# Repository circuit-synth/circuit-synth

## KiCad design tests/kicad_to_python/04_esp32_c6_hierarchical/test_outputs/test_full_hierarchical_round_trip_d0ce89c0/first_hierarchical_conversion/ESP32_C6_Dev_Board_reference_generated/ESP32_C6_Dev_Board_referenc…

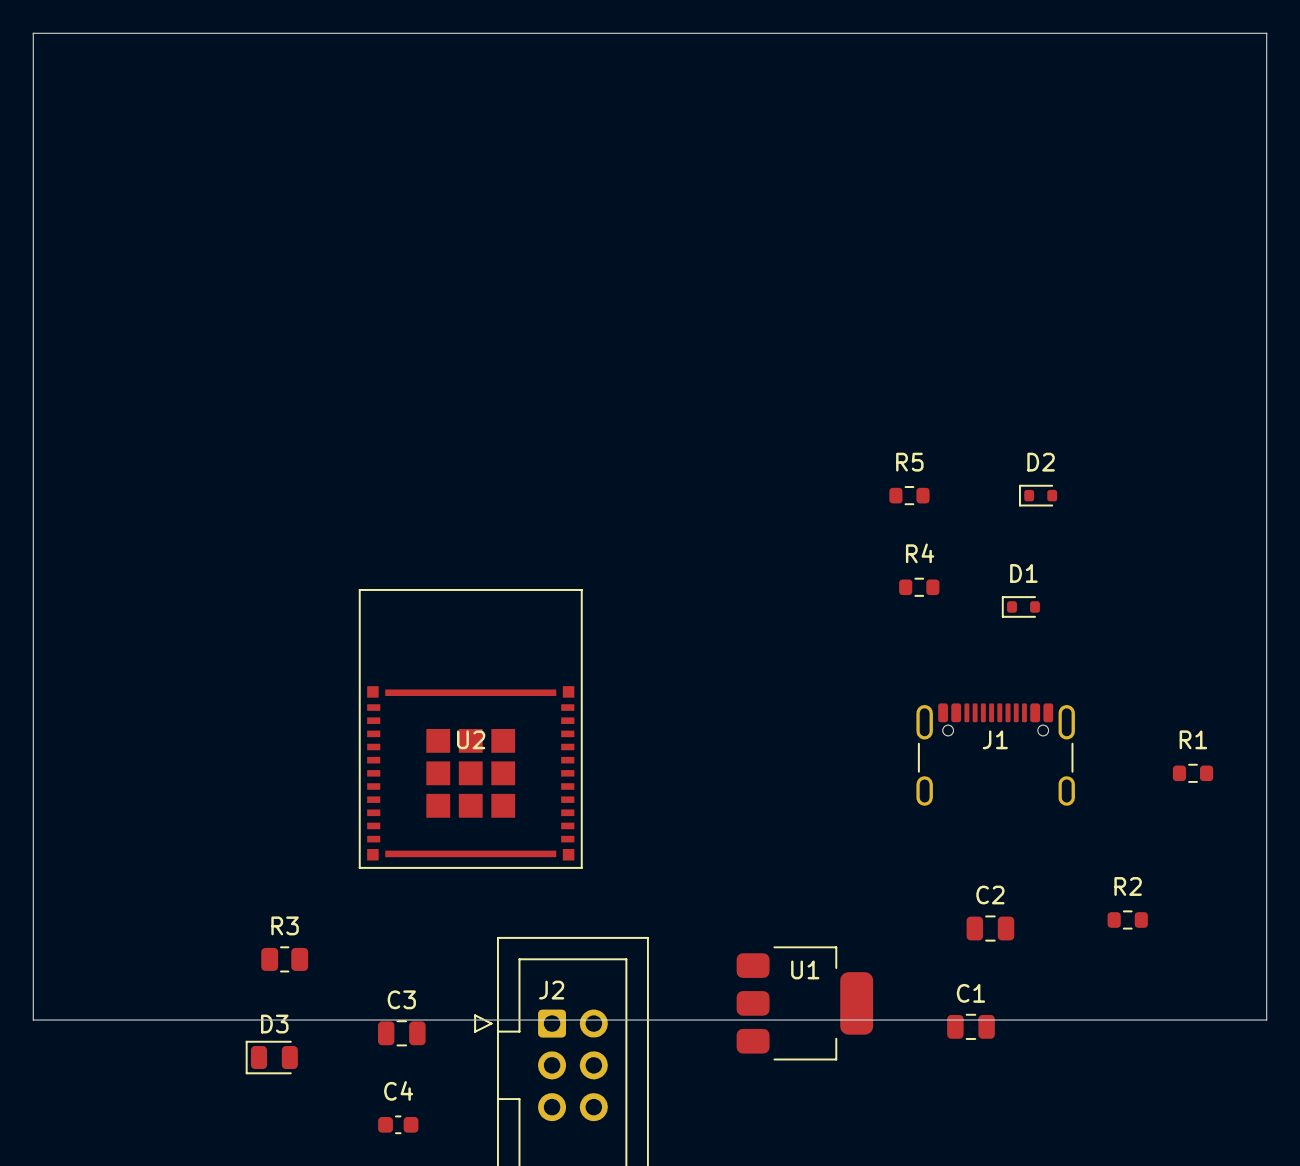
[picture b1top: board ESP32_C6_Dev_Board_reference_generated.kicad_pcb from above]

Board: 2 copper layers, 75.0 x 60.0 mm, 16 parts (0 on the bottom side), 15 nets, no tracks yet.

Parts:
C1, C2: 10uF; C_0805_2012Metric
C3: 22uF; C_0805_2012Metric
C4: 100nF; C_0603_1608Metric
D1, D2: D_SOD-523
D3: LED_0805_2012Metric
J1: USB_C_Receptacle_GCT_USB4105-xx-A_16P_TopMnt_Horizontal
J2: IDC-Header_2x03_P2.54mm_Vertical
R1, R2: 5.1k; R_0603_1608Metric
R3: 330; R_0805_2012Metric
R4, R5: 22; R_0603_1608Metric
U1: SOT-223-3_TabPin2
U2: ESP32-C6-MINI-1

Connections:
DEBUG_EN: J2.1, U2.8
DEBUG_IO0: J2.6, U2.12
DEBUG_RX: J2.5, U2.30
DEBUG_TX: J2.3, U2.31
ESP32_C6_MCU/N$3: D3.2, R3.2
GND: C1.2, C2.2, C3.2, C4.2, D1.2, D2.2, D3.1, J1.A1, J1.A12, J1.B1, J1.B12, J1.S1, J2.4, R1.2, R2.2, U1.1, U2.1, U2.2, U2.11, U2.14, U2.36, U2.37, U2.38, U2.39, U2.40, U2.41, U2.42, U2.43, U2.44, U2.45, U2.46, U2.47, U2.48, U2.49, U2.50, U2.51, U2.52, U2.53
LED_CONTROL: R3.1, U2.22
unnamed: J1.A5, R1.1
unnamed: J1.B5, R2.1
USB_DM: D2.1, J1.A7, R5.1
USB_DM_MCU: R5.2, U2.25
USB_DP: D1.1, J1.A6, R4.1
USB_DP_MCU: R4.2, U2.24
VBUS: C1.1, C2.1, J1.A4, J1.A9, J1.B4, J1.B9, U1.3
VCC_3V3: C3.1, C4.1, J2.2, U1.2, U2.3
